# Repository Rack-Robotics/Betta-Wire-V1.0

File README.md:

# Betta-Wire-V1.0
Betta-Wire V1.0 is an affordable, open-source wire EDM machine designed for enthusiats. It allows users to cut electrically conductive materials such as steel and aluminum without the need for expensive industrial equipment like fiber lasers or CNC machines.

## Features 

- **Open Source**: Fully open-source design, allowing for community contributions and custom modifications.
- **User-3D-Printed**: Most components can be 3D printed, making it accessible and customizable.
- **Powercore Compatible**: Compatible with Powercore V2.0 EDM power supply.
- **4-Axis Motion**: Top and bottom EDM tools are capable of indepedent motion for X, Y, U, & V motion. 
- **Compact Build Area**: 100mm x 200mm, suitable for moderate-scale projects.
- **Hole Popping**: Cut starter holes for enclosed profiles using 1mm diameter hole popping electrodes.
- **Assisted Threading**: Easy controls for beginning threading and for detecting successful threading.
- **Material Compatibility**: Capable of cutting aluminum, steel, titanium, and other electrically conductive materials.

## Revisions 

### RevA

RevA is the prototype proof-of-concept version of the Betta-Wire V1.0. It served as the initial platform to test and validate the core functionality of the machine. While functional, it lacks some of the refinements and optimizations planned for the final kit version.

### RevB

RevB is the branch for the final version that will be used for the kit. This version includes all the improvements and optimizations based on the learnings from RevA. It is intended for distribution to users who will assemble the Betta-Wire V1.0 from the kit.

## Recommended Prerequisites

- 3D Printer (capable of printing carbon fiber PLA)
- Basic understanding of mechatronics and 3D printing
- Familiarity with Klipper firmware
 
 ## Legal & License

Shield: [![CC BY-NC 4.0][cc-by-nc-shield]][cc-by-nc]

This work is licensed under a
[Creative Commons Attribution-NonCommercial 4.0 International License][cc-by-nc].

[![CC BY-NC 4.0][cc-by-nc-image]][cc-by-nc]

[cc-by-nc]: https://creativecommons.org/licenses/by-nc/4.0/
[cc-by-nc-image]: https://licensebuttons.net/l/by-nc/4.0/88x31.png
[cc-by-nc-shield]: https://img.shields.io/badge/License-CC%20BY--NC%204.0-lightgrey.svg

You are free to:
- Share — copy and redistribute the material in any medium or format
- Adapt — remix, transform, and build upon the material

Under the following terms:
- Attribution — You must give appropriate credit, provide a link to the license, and indicate if changes were made. You may do so in any reasonable manner, but not in any way that suggests the licensor endorses you or your use.
- NonCommercial — You may not use the material for commercial purposes.

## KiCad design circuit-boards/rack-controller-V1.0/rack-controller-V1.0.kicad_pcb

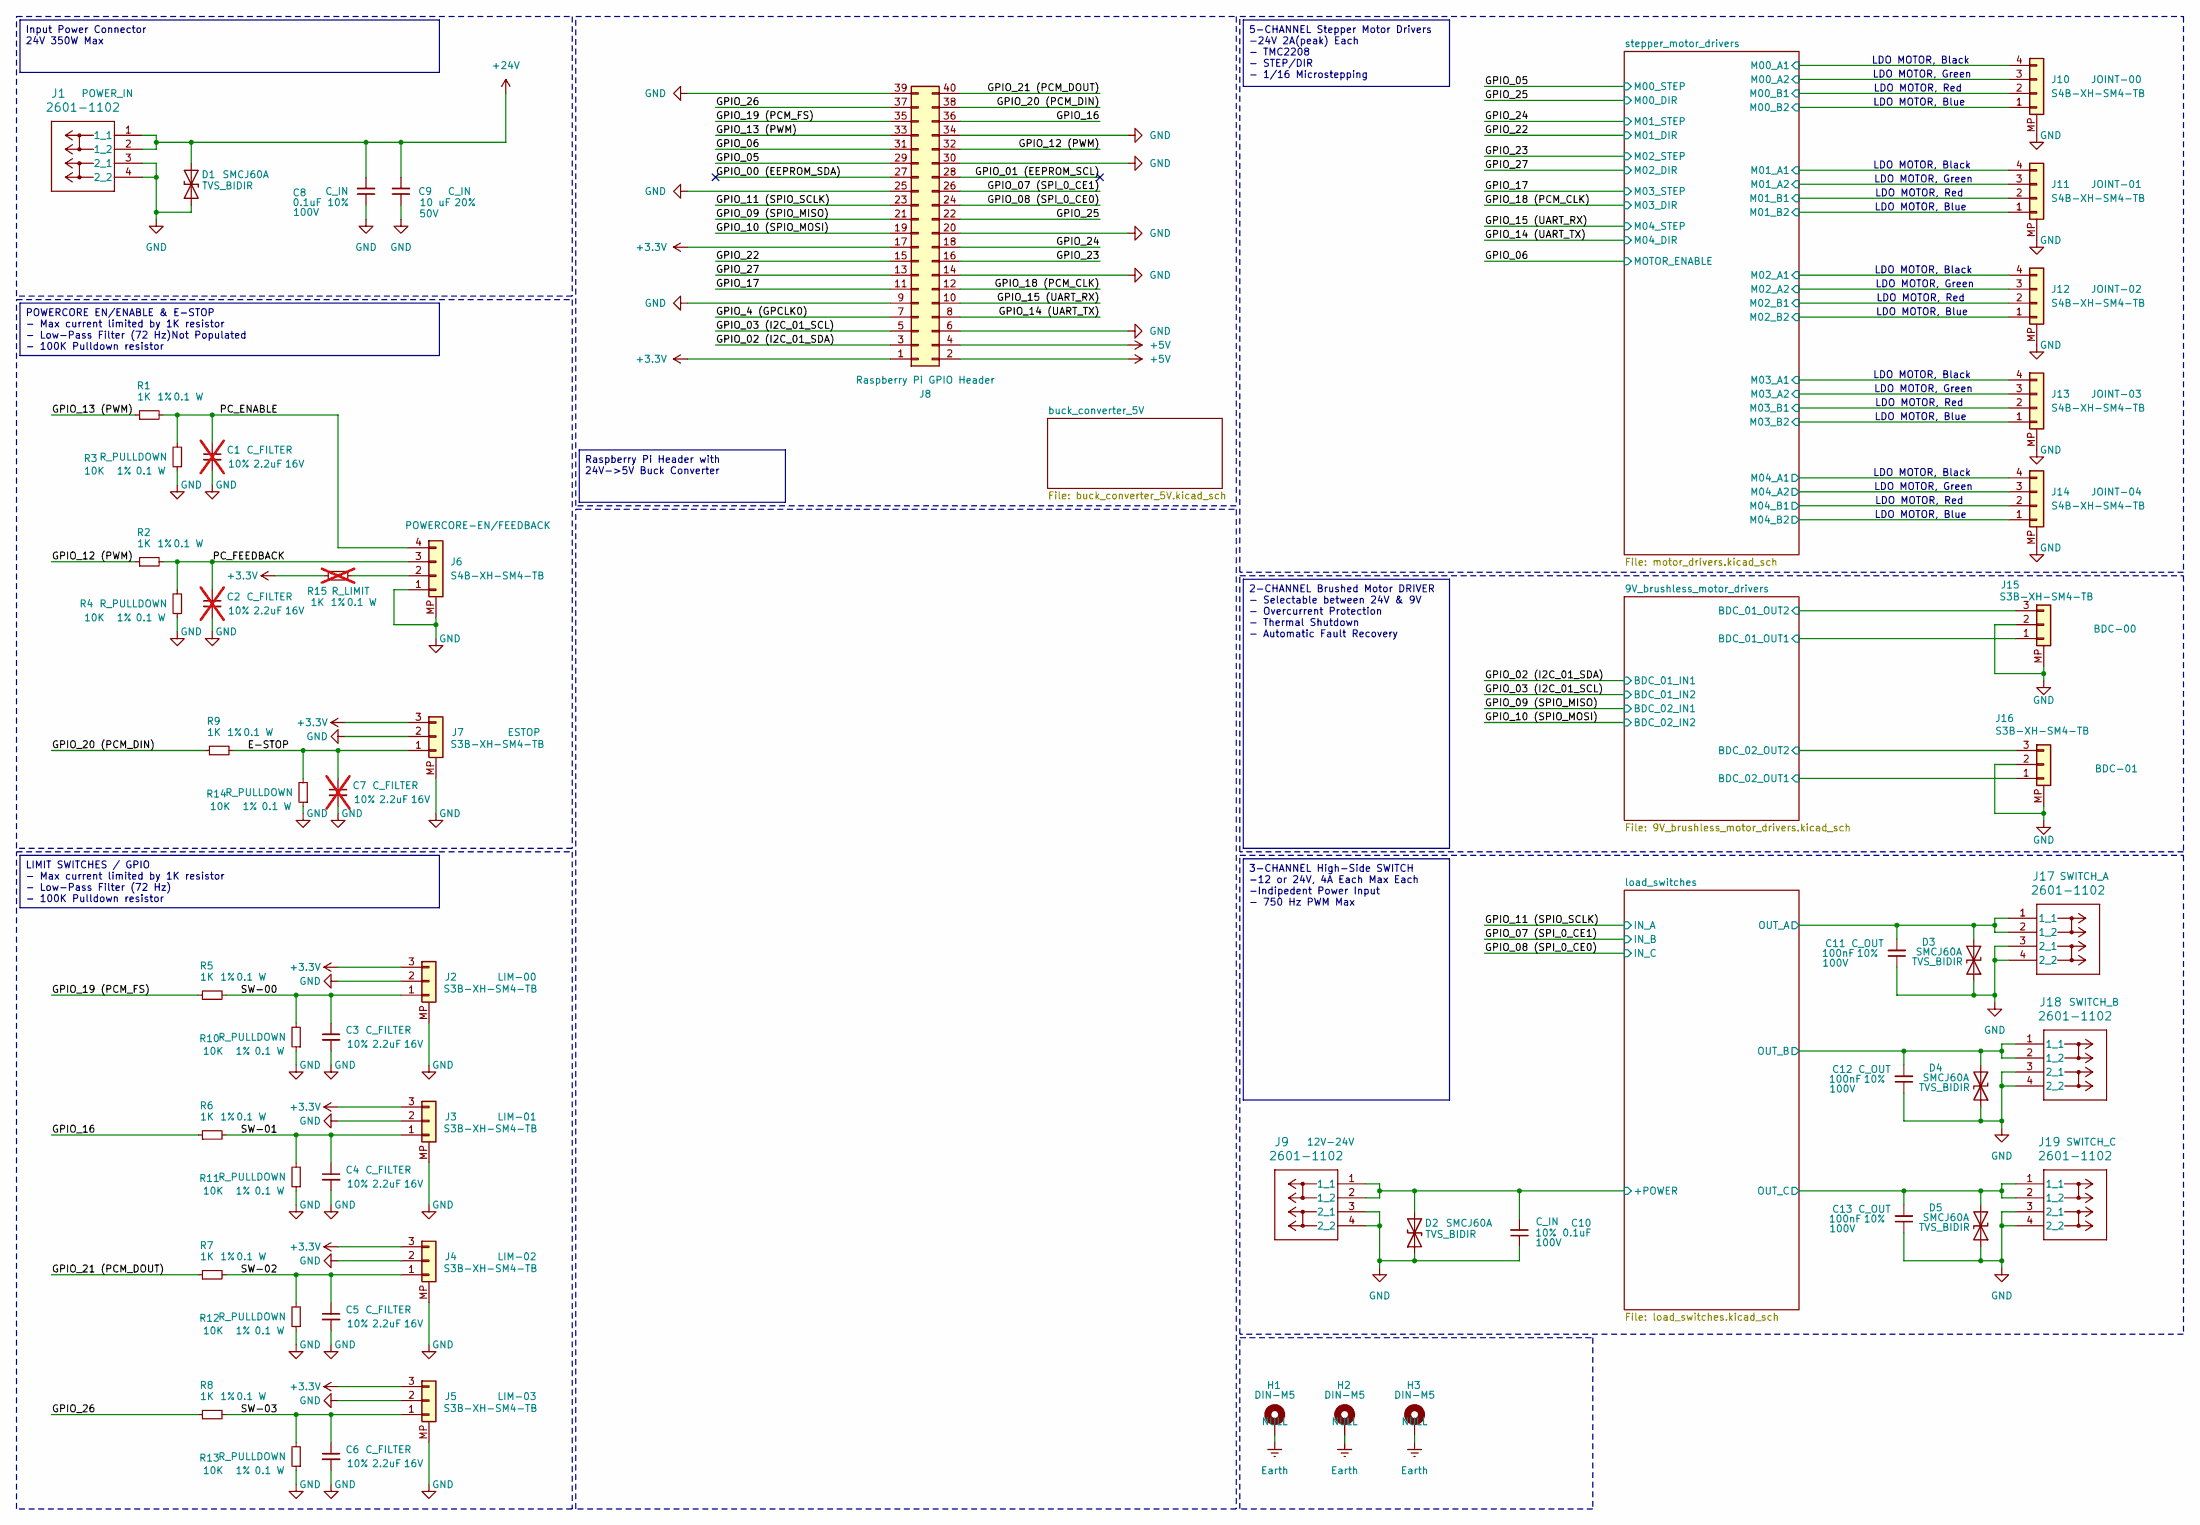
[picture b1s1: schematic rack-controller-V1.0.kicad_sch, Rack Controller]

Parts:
C1, C2, C7: 2.2uF; C_0603_1608Metric; Max Voltage 16V; Tolerance 10%; Manufacturer# CC0603KRX5R7BB225; LCSC Part # C106853; not fitted
C3, C4, C5, C6: 2.2uF; C_0603_1608Metric; Max Voltage 16V; Tolerance 10%; Manufacturer# CC0603KRX5R7BB225; LCSC Part # C106853
C8, C10: 0.1uF; C_0603_1608Metric; Tolerance 10%; Max Voltage 100V; Manufacturer# CC0603KRX7R0BB104; LCSC Part # C113803
C9: 10 uF; C_1206_3216Metric; Tolerance 20%; Max Voltage 50V; Manufacturer# CL31A106MBHNNNE; LCSC Part # C96600
C11, C12, C13: 100nF; C_0603_1608Metric; Voltage 100V; Tolerance 10%; Manufacturer# CC0603KRX7R0BB104; LCSC Part # C113803
D1, D2, D3, D4, D5: SMCJ60A; D_SMC; Manufacturer# SMCJ60CA-13-F; LCSC Part # C2943780
H1, H2, H3: DIN-M5; MountingHole_5.3mm_M5_DIN965_Pad_TopBottom; Manufacturer# NULL; LCSC Part # NULL
J1, J9, J17, J18, J19: 2601-1102; Manufacturer# 2601-1102
J2, J3, J4, J5, J7, J15, J16: S3B-XH-SM4-TB; Manufacturer# JST Sales America Inc.; LCSC Part # C161860
J6, J10, J11, J12, J13, J14: S4B-XH-SM4-TB; JST_XH_S4B-XH-SM4-TB_1x04-1MP_P2.50mm_Horizontal_custom; Manufacturer# S4B-XH-SM4-TB; LCSC Part # C161861
J8: Raspberry Pi GPIO Header; raspberrypi; Manufacturer# ESQ-120-23-T-D; LCSC Part # NULL
R1, R2, R5, R6, R7, R8, R9: 1K; R_0603_1608Metric; Tolerance 1%; Manufacturer# RC0603FR-071KL; LCSC Part # C22548
R3, R4, R10, R11, R12, R13, R14: 10K; R_0603_1608Metric; Tolerance 1%; Manufacturer# RC0603BR-0710KL; LCSC Part # C98220
R15: 1K; R_0603_1608Metric; Tolerance 1%; Manufacturer# RC0603FR-071KL; LCSC Part # C22548; not fitted

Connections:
+3.3V: J2.3, J3.3, J4.3, J5.3, J7.3, J8.1, J8.17, R15.1; also elsewhere on the board
+5V: J8.2, J8.4; also elsewhere on the board
+24V: C8.2, C9.2, D1.2 (A2), J1.1 (1_1), J1.2 (1_2); also elsewhere on the board
/9V_brushless_motor_drivers/BDC_01_OUT1: J15.1; also elsewhere on the board
/9V_brushless_motor_drivers/BDC_01_OUT2: J15.3; also elsewhere on the board
/9V_brushless_motor_drivers/BDC_02_OUT1: J16.1; also elsewhere on the board
/9V_brushless_motor_drivers/BDC_02_OUT2: J16.3; also elsewhere on the board
/E-STOP: C7.1, J7.1, R9.2, R14.2
/GPIO_00 (EEPROM_SDA): J8.27
/GPIO_01 (EEPROM_SCL): J8.28
/GPIO_02 (I2C_01_SDA): J8.3; also elsewhere on the board
/GPIO_03 (I2C_01_SCL): J8.5; also elsewhere on the board
/GPIO_4 (GPCLK0): J8.7
/GPIO_05: J8.29; also elsewhere on the board
/GPIO_06: J8.31; also elsewhere on the board
/GPIO_07 (SPI_0_CE1): J8.26; also elsewhere on the board
/GPIO_08 (SPI_0_CE0): J8.24; also elsewhere on the board
/GPIO_09 (SPIO_MISO): J8.21; also elsewhere on the board
/GPIO_10 (SPIO_MOSI): J8.19; also elsewhere on the board
/GPIO_11 (SPIO_SCLK): J8.23; also elsewhere on the board
/GPIO_12 (PWM): J8.32, R2.1
/GPIO_13 (PWM): J8.33, R1.1
/GPIO_14 (UART_TX): J8.8; also elsewhere on the board
/GPIO_15 (UART_RX): J8.10; also elsewhere on the board
/GPIO_16: J8.36, R6.1
/GPIO_17: J8.11; also elsewhere on the board
/GPIO_18 (PCM_CLK): J8.12; also elsewhere on the board
/GPIO_19 (PCM_FS): J8.35, R5.1
/GPIO_20 (PCM_DIN): J8.38, R9.1
/GPIO_21 (PCM_DOUT): J8.40, R7.1
/GPIO_22: J8.15; also elsewhere on the board
/GPIO_23: J8.16; also elsewhere on the board
/GPIO_24: J8.18; also elsewhere on the board
/GPIO_25: J8.22; also elsewhere on the board
/GPIO_26: J8.37, R8.1
/GPIO_27: J8.13; also elsewhere on the board
/PC_ENABLE: C1.1, J6.4, R1.2, R3.2
/PC_FEEDBACK: C2.1, J6.3, R2.2, R4.2
/SW-00: C3.1, J2.1, R5.2, R10.2
/SW-01: C4.1, J3.1, R6.2, R11.2
/SW-02: C5.1, J4.1, R7.2, R12.2
/SW-03: C6.1, J5.1, R8.2, R13.2
/load_switches/+POWER: C10.2, D2.2 (A2), J9.1 (1_1), J9.2 (1_2); also elsewhere on the board
/load_switches/OUT_A: C11.2, D3.2 (A2), J17.1 (1_1), J17.2 (1_2); also elsewhere on the board
/load_switches/OUT_B: C12.2, D4.2 (A2), J18.1 (1_1), J18.2 (1_2); also elsewhere on the board
/load_switches/OUT_C: C13.2, D5.2 (A2), J19.1 (1_1), J19.2 (1_2); also elsewhere on the board
/stepper_motor_drivers/M00_A1: J10.4; also elsewhere on the board
/stepper_motor_drivers/M00_A2: J10.3; also elsewhere on the board
/stepper_motor_drivers/M00_B1: J10.2; also elsewhere on the board
/stepper_motor_drivers/M00_B2: J10.1; also elsewhere on the board
/stepper_motor_drivers/M01_A1: J11.4; also elsewhere on the board
/stepper_motor_drivers/M01_A2: J11.3; also elsewhere on the board
/stepper_motor_drivers/M01_B1: J11.2; also elsewhere on the board
/stepper_motor_drivers/M01_B2: J11.1; also elsewhere on the board
/stepper_motor_drivers/M02_A1: J12.4; also elsewhere on the board
/stepper_motor_drivers/M02_A2: J12.3; also elsewhere on the board
/stepper_motor_drivers/M02_B1: J12.2; also elsewhere on the board
/stepper_motor_drivers/M02_B2: J12.1; also elsewhere on the board
/stepper_motor_drivers/M03_A1: J13.4; also elsewhere on the board
/stepper_motor_drivers/M03_A2: J13.3; also elsewhere on the board
/stepper_motor_drivers/M03_B1: J13.2; also elsewhere on the board
/stepper_motor_drivers/M03_B2: J13.1; also elsewhere on the board
/stepper_motor_drivers/M04_A1: J14.4; also elsewhere on the board
/stepper_motor_drivers/M04_A2: J14.3; also elsewhere on the board
/stepper_motor_drivers/M04_B1: J14.2; also elsewhere on the board
/stepper_motor_drivers/M04_B2: J14.1; also elsewhere on the board
Earth: H1.1, H2.1, H3.1
GND: C1.2, C2.2, C3.2, C4.2, C5.2, C6.2, C7.2, C8.1, C9.1, C10.1, C11.1, C12.1, C13.1, D1.1 (A1), D2.1 (A1), D3.1 (A1), D4.1 (A1), D5.1 (A1), J1.3 (2_1), J1.4 (2_2), J2.2, J2.MP, J3.2, J3.MP, J4.2, J4.MP, J5.2, J5.MP, J6.1, J6.MP, J7.2, J7.MP, J8.6, J8.9, J8.14, J8.20, J8.25, J8.30, J8.34, J8.39, J9.3 (2_1), J9.4 (2_2), J10.MP, J11.MP, J12.MP, J13.MP, J14.MP, J15.2, J15.MP, J16.2, J16.MP, J17.3 (2_1), J17.4 (2_2), J18.3 (2_1), J18.4 (2_2), J19.3 (2_1), J19.4 (2_2), R3.1, R4.1, R10.1, R11.1, R12.1, R13.1, R14.1; also elsewhere on the board
unnamed: J6.2, R15.2

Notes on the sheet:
LDO MOTOR, Green
LDO MOTOR, Blue
LDO MOTOR, Black
LDO MOTOR, Red
2-CHANNEL Brushed Motor DRIVER - Selectable between 24V & 9V - Overcurrent Protection - Thermal Shutdown - Automatic Fault Recovery
LIMIT SWITCHES / GPIO - Max current limited by 1K resistor - Low-Pass Filter (72 Hz) - 100K Pulldown resistor
5-CHANNEL Stepper Motor Drivers -24V 2A(peak) Each - TMC2208 - STEP/DIR - 1/16 Microstepping
POWERCORE EN/ENABLE & E-STOP - Max current limited by 1K resistor - Low-Pass Filter (72 Hz)Not Populated - 100K Pulldown resistor
3-CHANNEL High-Side SWITCH -12 or 24V, 4A Each Max Each -Indipedent Power Input - 750 Hz PWM Max
Input Power Connector 24V 350W Max
Raspberry Pi Header with 24V->5V Buck Converter

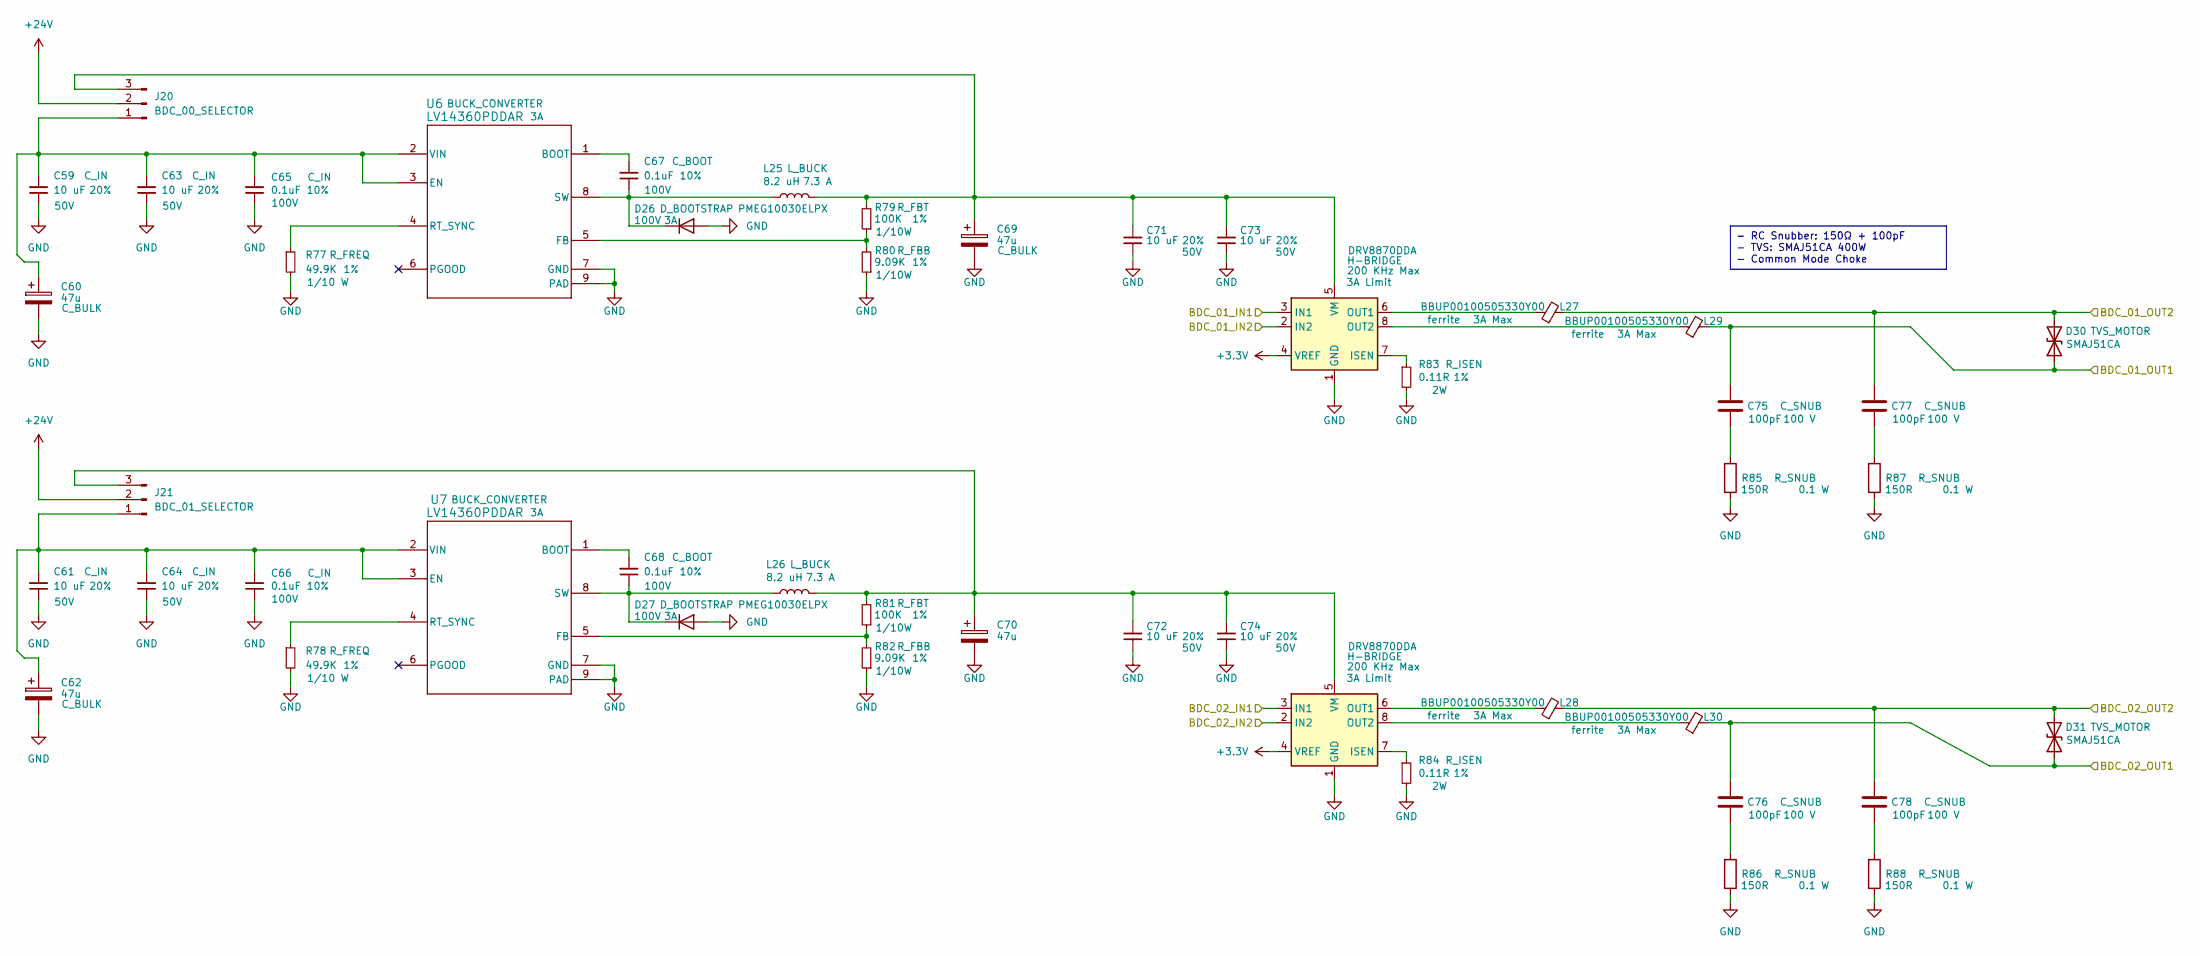
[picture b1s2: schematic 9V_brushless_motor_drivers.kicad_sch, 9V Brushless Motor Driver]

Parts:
C59, C61, C63, C64, C71, C72, C73, C74: 10 uF; C_1206_3216Metric; Tolerance 20%; Max Voltage 50V; Manufacturer# CL31A106MBHNNNE; LCSC Part # C96600
C60, C62, C69, C70: 47u; CP_Elec_6.3x5.9; Manufacturer# 35SVPK47M; LCSC Part # C264034
C65, C66, C67, C68: 0.1uF; C_0603_1608Metric; Tolerance 10%; Max Voltage 100V; Manufacturer# CC0603KRX7R0BB104; LCSC Part # C113803
C75, C76, C77, C78: 100pF; C_0402_1005Metric; Voltage 100 V; Manufacturer# CC0402JRNPO0BN101; LCSC Part # C576700
D26, D27: PMEG10030ELPX; D_SOD-128; Max Voltage 100V; Manufacturer# PMEG10030ELPX; LCSC Part # C5260346
D30, D31: SMAJ51CA; D_SMA; Manufacturer# SMAJ60CA-13-F; LCSC Part # C135003
J20: BDC_00_SELECTOR; PinHeader_1x03_P2.54mm_Vertical; Manufacturer# PZ2.54-1*3; LCSC Part # C5360899
J21: BDC_01_SELECTOR; PinHeader_1x03_P2.54mm_Vertical; Manufacturer# PZ2.54-1*3; LCSC Part # C5360899
L25, L26: 8.2 uH; SRR1210-8R2Y; Manufacturer# SRR1210-8R2Y
L27, L28, L29, L30: BBUP00100505330Y00; L_0402_1005Metric; Manufacturer# BLM15AX100SN1D; LCSC Part # C668299
R77, R78: 49.9K; R_0603_1608Metric; Tolerance 1%; Manufacturer# RC0603FR-0749K9L
R79, R81: 100K; R_0603_1608Metric; Tolerance 1%; Manufacturer# RT0603FRE07100KL; LCSC Part # C728638
R80, R82: 9.09K; R_0603_1608Metric; Tolerance 1%; Manufacturer# RC0603FR-079K09L; LCSC Part # C185301
R83, R84: 0.11R; R_2512_6332Metric; Tolerance 1%; Manufacturer# YHR2512SE2WR110F4; LCSC Part # C46595965
R85, R86, R87, R88: 150R; R_0603_1608Metric; Tolerance 1%; Manufacturer# RC0603FR-07150RL; LCSC Part # C114608
U6, U7: LV14360PDDAR; Manufacturer# LV14360PDDAR; LCSC Part # C2864599
U8, U9: DRV8870DDA; Manufacturer# DRV8870DDAR; LCSC Part # C86590

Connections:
+3.3V: U8.4 (VREF), U9.4 (VREF); also elsewhere on the board
+24V: J20.2, J21.2; also elsewhere on the board
/9V_brushless_motor_drivers/BDC_01_OUT1: C75.1, D30.1 (A1), L29.2; also elsewhere on the board
/9V_brushless_motor_drivers/BDC_01_OUT2: C77.1, D30.2 (A2), L27.2; also elsewhere on the board
/9V_brushless_motor_drivers/BDC_02_OUT1: C76.1, D31.1 (A1), L30.2; also elsewhere on the board
/9V_brushless_motor_drivers/BDC_02_OUT2: C78.1, D31.2 (A2), L28.2; also elsewhere on the board
/GPIO_02 (I2C_01_SDA): U8.3 (IN1); also elsewhere on the board
/GPIO_03 (I2C_01_SCL): U8.2 (IN2); also elsewhere on the board
/GPIO_09 (SPIO_MISO): U9.3 (IN1); also elsewhere on the board
/GPIO_10 (SPIO_MOSI): U9.2 (IN2); also elsewhere on the board
GND: C59.1, C60.2, C61.1, C62.2, C63.1, C64.1, C65.1, C66.1, C69.2, C70.2, C71.1, C72.1, C73.1, C74.1, D26.2 (A), D27.2 (A), R77.2, R78.2, R80.1, R82.1, R83.2, R84.2, R85.2, R86.2, R87.2, R88.2, U6.7 (GND), U6.9 (PAD), U7.7 (GND), U7.9 (PAD), U8.1 (GND), U8.9 (GND), U9.1 (GND), U9.9 (GND); also elsewhere on the board
unnamed: C75.2, R85.1
unnamed: C76.2, R86.1
unnamed: C77.2, R87.1
unnamed: C78.2, R88.1
unnamed: C67.1, D26.1 (K), L25.1, U6.8 (SW)
unnamed: C68.1, D27.1 (K), L26.1, U7.8 (SW)
unnamed: C59.2, C60.1, C63.2, C65.2, J20.1, U6.2 (VIN), U6.3 (EN)
unnamed: C69.1, C71.2, C73.2, J20.3, L25.2, R79.2, U8.5 (VM)
unnamed: C61.2, C62.1, C64.2, C66.2, J21.1, U7.2 (VIN), U7.3 (EN)
unnamed: C70.1, C72.2, C74.2, J21.3, L26.2, R81.2, U9.5 (VM)
unnamed: C67.2, U6.1 (BOOT)
unnamed: R79.1, R80.2, U6.5 (FB)
unnamed: R77.1, U6.4 (RT_SYNC)
unnamed: C68.2, U7.1 (BOOT)
unnamed: R81.1, R82.2, U7.5 (FB)
unnamed: R78.1, U7.4 (RT_SYNC)
unnamed: R83.1, U8.7 (ISEN)
unnamed: L27.1, U8.6 (OUT1)
unnamed: L29.1, U8.8 (OUT2)
unnamed: R84.1, U9.7 (ISEN)
unnamed: L28.1, U9.6 (OUT1)
unnamed: L30.1, U9.8 (OUT2)

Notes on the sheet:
- RC Snubber: 150Ω + 100pF - TVS: SMAJ51CA 400W - Common Mode Choke

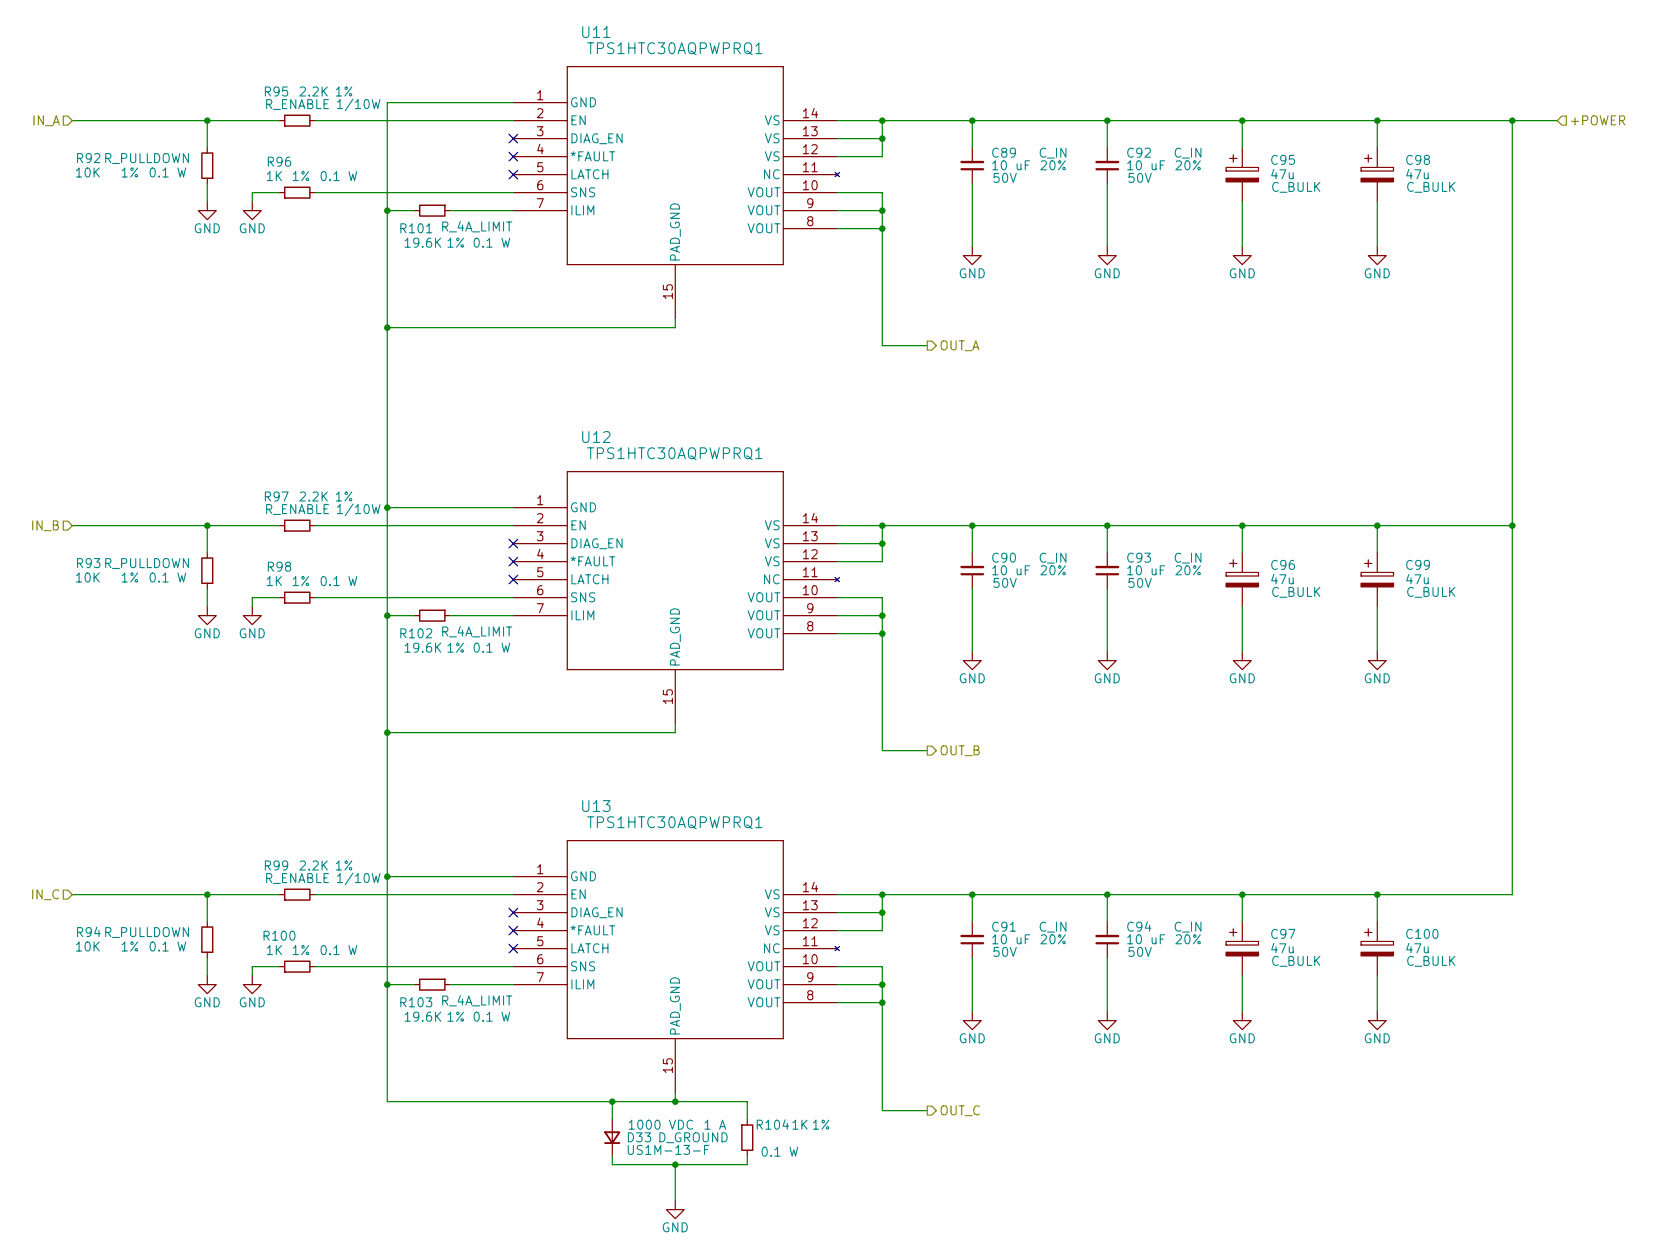
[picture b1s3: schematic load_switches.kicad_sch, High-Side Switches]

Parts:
C89, C90, C91, C92, C93, C94: 10 uF; C_1206_3216Metric; Tolerance 20%; Max Voltage 50V; Manufacturer# CL31A106MBHNNNE; LCSC Part # C96600
C95, C96, C97, C98, C99, C100: 47u; CP_Elec_6.3x5.9; Manufacturer# 35SVPK47M; LCSC Part # C264034
D33: US1M-13-F; D_SMA; Tolerance NULL; Manufacturer# US1M-13-F; LCSC Part # C99333
R92, R93, R94: 10K; R_0603_1608Metric; Tolerance 1%; Manufacturer# RC0603BR-0710KL; LCSC Part # C98220
R95, R97, R99: 2.2K; R_0603_1608Metric; Tolerance 1%; Manufacturer# RC0603FR-072K2L; LCSC Part # C114662
R96, R98, R100, R104: 1K; R_0603_1608Metric; Tolerance 1%; Manufacturer# RC0603FR-071KL; LCSC Part # C22548
R101, R102, R103: 19.6K; R_0603_1608Metric; Tolerance 1%; Manufacturer# RC0603FR-0719K6L; LCSC Part # C245925
U11, U12, U13: TPS1HTC30AQPWPRQ1; TPS1HTC30-Q1; Manufacturer# TPS1HTC30AQPWPRQ1; LCSC Part # C22414694

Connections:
/GPIO_07 (SPI_0_CE1): R93.2, R97.1; also elsewhere on the board
/GPIO_08 (SPI_0_CE0): R94.2, R99.1; also elsewhere on the board
/GPIO_11 (SPIO_SCLK): R92.2, R95.1; also elsewhere on the board
/load_switches/+POWER: C89.2, C90.2, C91.2, C92.2, C93.2, C94.2, C95.1, C96.1, C97.1, C98.1, C99.1, C100.1, U11.12 (VS), U11.13 (VS), U11.14 (VS), U12.12 (VS), U12.13 (VS), U12.14 (VS), U13.12 (VS), U13.13 (VS), U13.14 (VS); also elsewhere on the board
/load_switches/OUT_A: U11.8 (VOUT), U11.9 (VOUT), U11.10 (VOUT); also elsewhere on the board
/load_switches/OUT_B: U12.8 (VOUT), U12.9 (VOUT), U12.10 (VOUT); also elsewhere on the board
/load_switches/OUT_C: U13.8 (VOUT), U13.9 (VOUT), U13.10 (VOUT); also elsewhere on the board
GND: C89.1, C90.1, C91.1, C92.1, C93.1, C94.1, C95.2, C96.2, C97.2, C98.2, C99.2, C100.2, D33.1 (K), R92.1, R93.1, R94.1, R96.1, R98.1, R100.1, R104.2; also elsewhere on the board
unnamed: D33.2 (A), R101.2, R102.2, R103.2, R104.1, U11.1 (GND), U11.15 (PAD_GND), U12.1 (GND), U12.15 (PAD_GND), U13.1 (GND), U13.15 (PAD_GND)
unnamed: R95.2, U11.2 (EN)
unnamed: R101.1, U11.7 (ILIM)
unnamed: R96.2, U11.6 (SNS)
unnamed: R97.2, U12.2 (EN)
unnamed: R102.1, U12.7 (ILIM)
unnamed: R98.2, U12.6 (SNS)
unnamed: R99.2, U13.2 (EN)
unnamed: R103.1, U13.7 (ILIM)
unnamed: R100.2, U13.6 (SNS)
